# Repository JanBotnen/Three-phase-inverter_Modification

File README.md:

# Three-phase-inverter_Modification

**Design and implementation of a three-phase inverter with SPWM and SVPWM, prepared for future PMSM control.**

## Background
This project focuses on the continued development and modification of a three-phase DC-to-AC converter, utilizing the Space Vector Pulse Width Modulation (SV-PWM) algorithm.
The inverter was originally designed and built by a previous bachelor group at the Western Norway University of Applied Sciences, and later further refined by another group who successfully reduced the physical footprint of the design.

Their thesis can be found at:
Version 1 : [HVL Open](https://hdl.handle.net/11250/3105460)
Version 2 : [HVL Open](https://hdl.handle.net/11250/3147156)

## About the Project

Building upon their work, our bachelor group aimed to prepare the inverter for future implementation of Field Oriented Control (FOC).  
Throughout this project, our primary goal has been to implement current measurement on all three phases and enable encoder input handling for rotor position feedback.

Our thesis can be found at: 
https://hdl.handle.net/11250/3202875

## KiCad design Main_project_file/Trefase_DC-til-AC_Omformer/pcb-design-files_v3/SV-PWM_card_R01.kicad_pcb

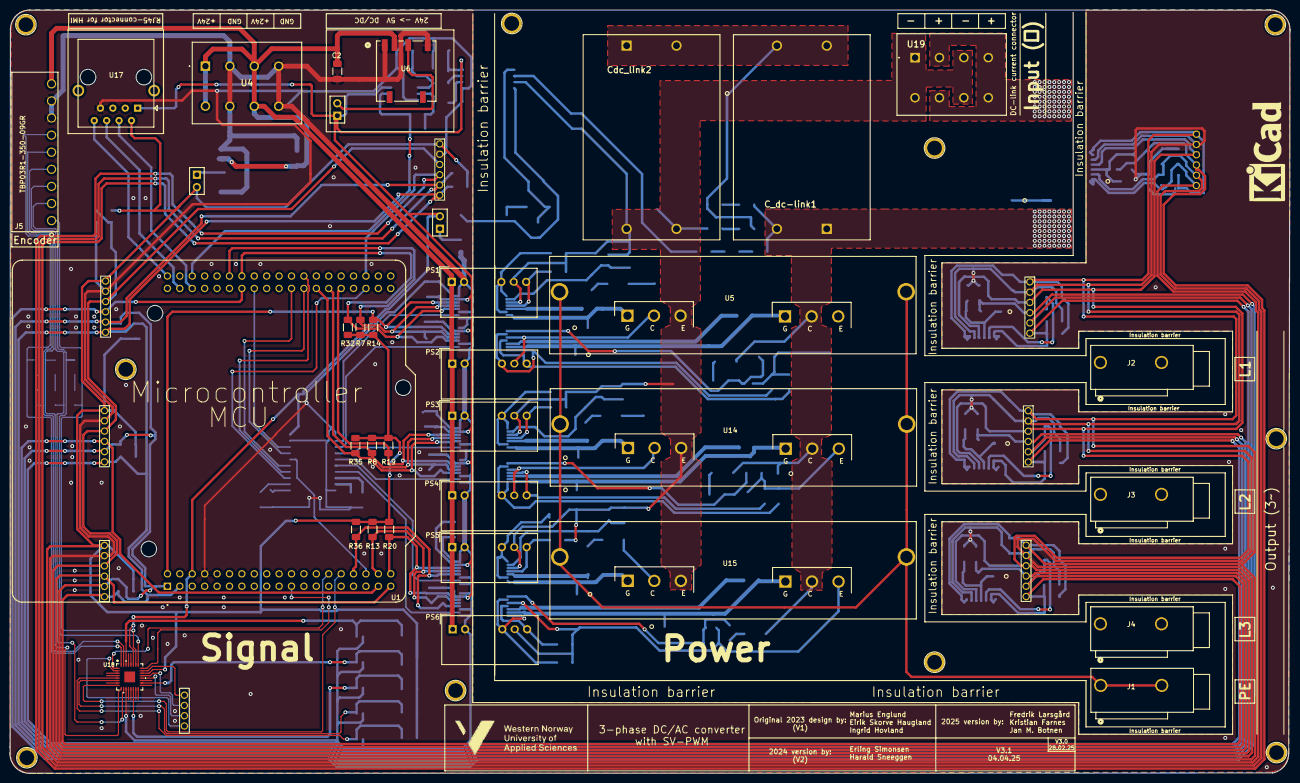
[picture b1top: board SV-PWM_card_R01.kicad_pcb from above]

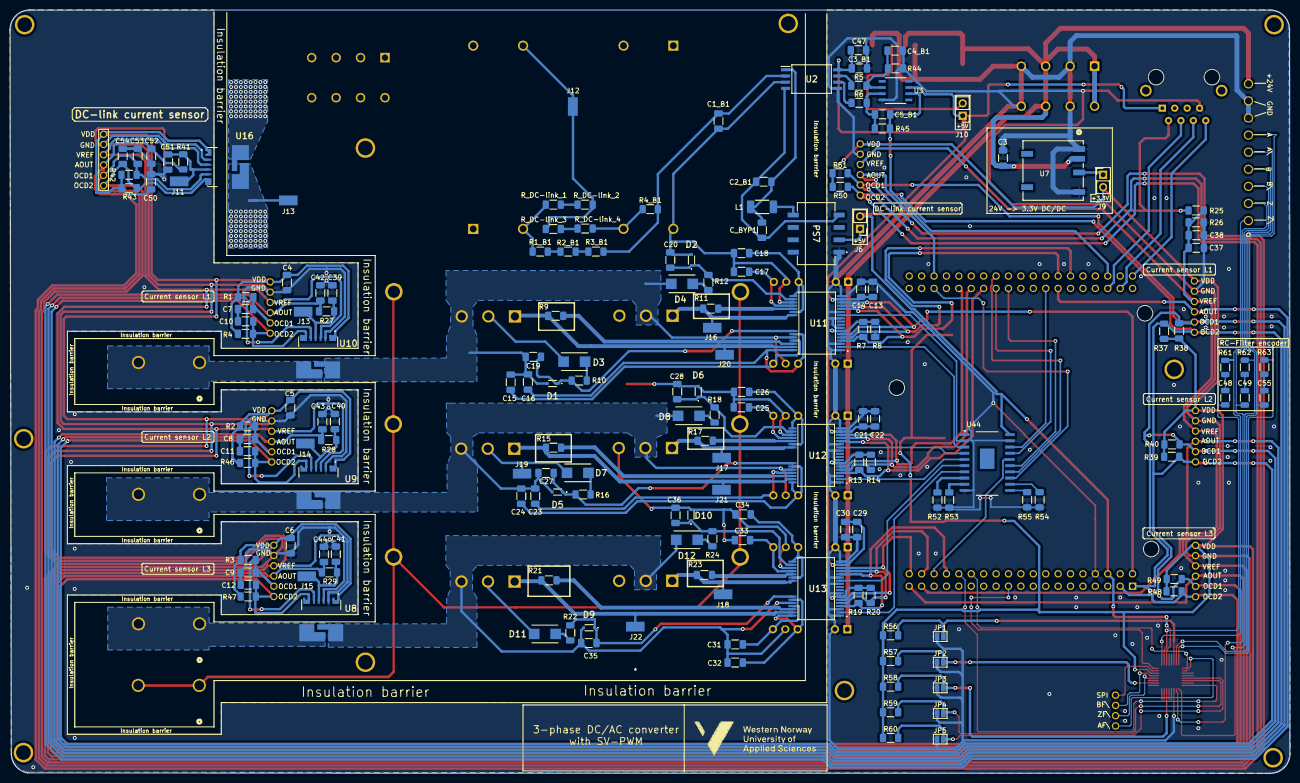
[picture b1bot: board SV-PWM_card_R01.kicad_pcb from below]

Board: 2 copper layers, 262.0 x 156.2 mm, 218 parts (168 on the bottom side), 126 nets.

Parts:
C1_B1: 100p; C_1206_3216Metric_Pad1.33x1.80mm_HandSolder
C2: 10u; C_1206_3216Metric_Pad1.33x1.80mm_HandSolder
C2_B1, C3_B1, C4_B1, C5_B1, C13, C14, C21, C22, C29, C30, C47: 100n; C_1206_3216Metric_Pad1.33x1.80mm_HandSolder
C3: 22u; C_1206_3216Metric_Pad1.33x1.80mm_HandSolder
C4, C5, C6, C50: 220n; C_1206_3216Metric_Pad1.33x1.80mm_HandSolder
C7, C8, C9, C10, C11, C12, C53, C54: 1n; C_1206_3216Metric_Pad1.33x1.80mm_HandSolder
C15, C16, C17, C18, C23, C24, C25, C26, C31, C32, C33, C34: 1u; C_1206_3216Metric_Pad1.33x1.80mm_HandSolder
C19, C20, C27, C28, C35, C36: 220p; C_1206_3216Metric_Pad1.33x1.80mm_HandSolder
C37, C38, C42, C43, C44, C52: 6.8n; C_1206_3216Metric_Pad1.33x1.80mm_HandSolder
C39, C40, C41, C51: 15n; C_1206_3216Metric_Pad1.33x1.80mm_HandSolder
C48, C49, C55: 100p; C_1206_3216Metric
C_BYP1: 4.7u; C_1206_3216Metric_Pad1.33x1.80mm_HandSolder
C_dc-link1: 14u; DC-link-capacitor-B32776G0146K000
Cdc_link2: 14u; DC-link-capacitor-B32776G0146K000
D1, D2, D5, D6, D9, D10: D_Schottky; Schottky-BAT165AX
D3, D4, D7, D8, D11, D12: D; Diode-SMBJ50CA
H6, H6#2, H6#3, H7, H7#2, H7#3, H7#4, H7#5, H7#6, H8: MountingHole; Skru-hull_3mm
J1, J2, J3, J4: WAGO_2606-1101; CONN_2606-1101_WAG
J5: TBP03R1-350-09GR; TBP03R1-350-03GR
J6, J9, J10: Conn_01x02_Male; PinHeader_1x02_P2.54mm_Vertical
J11, J12, J13, J13#2, J14, J15, J16, J17, J18, J19, J20, J21, J22: 5019; Keystone-5019
J23: 2606-1106/010-000; 6PinHeaderConnector_Strømsensor
JP1, JP2, JP3, JP4, JP5: SolderJumper_2_Open; SolderJumper-2_P1.3mm_Open_Pad1.0x1.5mm
L1: 47u; L_2010_5025Metric_Pad1.52x2.65mm_HandSolder
PS1, PS2, PS3, PS4, PS5, PS6: MGJ2D241509SC; Converter_DCDC_Murata_MGJ2DxxxxxxSC_THT
PS7: NTE0505MC; DC-DC-NTE0505MC
R1, R2, R3, R4, R7, R7#2, R8, R8#2, R13, R13#2, R14, R14#2, R19, R19#2, R20, R20#2, R32, R35, R36, R42, R43, R46, R47: 4.7k; R_1206_3216Metric_Pad1.30x1.75mm_HandSolder
R1_B1, R2_B1, R3_B1: 500k; R_1206_3216Metric_Pad1.30x1.75mm_HandSolder
R4_B1: 3.75k; R_1206_3216Metric_Pad1.30x1.75mm_HandSolder
R5, R6, R52, R53, R54, R55: 10k; R_1206_3216Metric_Pad1.30x1.75mm_HandSolder
R9, R11, R15, R17, R21, R23: 10; R_1206_3216Metric_Pad1.30x1.75mm_HandSolder
R10, R12, R16, R18, R22, R24, R25, R26: 1k; R_1206_3216Metric_Pad1.30x1.75mm_HandSolder
R27, R28, R29, R41: 220; R_1206_3216Metric_Pad1.30x1.75mm_HandSolder
R37, R38, R39, R40, R48, R49, R50, R51, R56, R57, R58, R59, R60: R; R_1206_3216Metric_Pad1.30x1.75mm_HandSolder
R44, R45: 16.5k; R_1206_3216Metric_Pad1.30x1.75mm_HandSolder
R61, R62, R63: 270; R_1206_3216Metric
R_DC-link_1, R_DC-link_2, R_DC-link_3, R_DC-link_4: ???; R_1206_3216Metric_Pad1.30x1.75mm_HandSolder
U1: MCU; MODULE_NUCLEO-L476RG
U2: ACPL-C87B-000E; ACPL-SOIC127P1150X331-8N
U3: type="X" model="OPAMP" lib=""; D8
U4, U19: Wago_2604-3104; WAGO-26043104
U5: Inverter leg nr 1; Inverter leg
U6: MP-K7805T-500R3; TRN 1&slash_3SM_SINGLE_TRP
U7: TRN 1-2410SM; TRN 1&slash_3SM_SINGLE_TRP
U8, U9, U10, U16: TLI4971A050T5UE0001XUMA1
U11, U12, U13: Infineon_2ED020I12-F2; GateDriver-2ED020I12F2XUMA1
U14: Inverter leg nr 2; Inverter leg
U15: Inverter leg nr 3; Inverter leg
U17: RJ45_Connector_MCU-til-HMI; RJ45_Amphenol_54602-x08_Horizontal
U18: MAX14890EATJ+T; 21-0140_T3255&plus_6_MXM_Encoder_chip
U36: PinConector_DC-link; 6PinHeaderConnector_Strømsensor
U37: PinConnector_L1-sensor; 6PinHeaderConnector_Strømsensor
U38: PinConnector_L2-sensor; 6PinHeaderConnector_Strømsensor
U39: PinConnector_L3-sensor; 6PinHeaderConnector_Strømsensor
U40: PinConector_MCU-til-L1; 6PinHeaderConnector_Strømsensor
U41: PinConnector_MCU-til-L2; 6PinHeaderConnector_Strømsensor
U42: PinConnector_MCU-til-L3; 6PinHeaderConnector_Strømsensor
U43: PinConnector_MCU-til-DClink; 6PinHeaderConnector_Strømsensor
U44: SN54HCT245_BusTranciver; ETSSOP-20-1EP_4.4x6.5mm_P0.65mm_EP3x4.2mm_ny123

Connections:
+3.3V: C4.1, C5.1, C6.1, C50.2, J9.1, J9.2, R1.1, R2.1, R3.1, R4.1, R7.1, R8.1, R13.1, R14.1, R19.1, R20.1, R25.1, R32.1, R35.1, R36.1, R37.1, R38.1, R39.1, R40.1, R42.1, R43.1, R46.1, R47.1, R48.1, R49.1, R50.1, R51.1, R56.1, R57.1, R58.1, R59.1, R60.1, U7.3 (NC), U8.1 (VDD), U9.1 (VDD), U10.1 (VDD), U16.1 (VDD), U17.2 (5V), U18.22 (VL), U36.1 (VDD), U37.1 (VDD), U38.1 (VDD), U39.1 (VDD), U40.1 (VDD), U41.1 (VDD), U42.1 (VDD), U43.1 (VDD)
+5V: C3_B1.1, C13.1, C14.2, C21.1, C22.2, C29.1, C30.2, C47.1, J6.2, J10.1, R7#2.2, R8#2.2, R13#2.2, R14#2.2, R19#2.2, R20#2.2, U1.CN7_6 (E5V), U2.8 (VDD2), U3.7, U11.7 (VCC1HS), U11.17 (VCC1LS), U12.7 (VCC1HS), U12.17 (VCC1LS), U13.7 (VCC1HS), U13.17 (VCC1LS), U17.1 (3.3V), U18.27 (VCC), U44.20 (VCC)
+5V_ISO: C2_B1.1, C_BYP1.1, L1.2, U2.1 (VDD1)
+15 V (1): C17.1, PS1.7 (+VOUT), U11.22 (VCC2LS)
+15 V (2): C15.2, PS2.7 (+VOUT), U11.33 (VCC2HS)
+15 V (3): C25.1, PS3.7 (+VOUT), U12.22 (VCC2LS)
+15 V (4): C23.2, PS4.7 (+VOUT), U12.33 (VCC2HS)
+15 V (5): C33.1, PS5.7 (+VOUT), U13.22 (VCC2LS)
+15 V (6): C31.2, PS6.7 (+VOUT), U13.33 (VCC2HS)
+24V: C2.1, C3.1, J5.9, PS1.1 (+VIN), PS2.1 (+VIN), PS3.1 (+VIN), PS4.1 (+VIN), PS5.1 (+VIN), PS6.1 (+VIN), U4.1, U4.2, U4.5, U4.6, U6.2 (+Vin), U7.2 (SENSE)
+DC-link: U16.8 (IP+), U19.3, U19.4, U19.7, U19.8
-8.7 V (1): C18.1, PS1.5 (-VOUT), U11.19 (VEE2LS), U11.24 (VEE2LS)
-8.7 V (2): C16.1, PS2.5 (-VOUT), U11.31 (VEE2HS), U11.36 (VEE2HS)
-8.7 V (3): C26.1, PS3.5 (-VOUT), U12.19 (VEE2LS), U12.24 (VEE2LS)
-8.7 V (4): C24.1, PS4.5 (-VOUT), U12.31 (VEE2HS), U12.36 (VEE2HS)
-8.7 V (5): C34.1, PS5.5 (-VOUT), U13.19 (VEE2LS), U13.24 (VEE2LS)
-8.7 V (6): C32.1, PS6.5 (-VOUT), U13.31 (VEE2HS), U13.36 (VEE2HS)
/CurrentMeasurement/L1 (out): J2.1, J2.2 (1), U10.7 (IP-)
/CurrentMeasurement/L2 (out): J3.1, J3.2 (1), U9.7 (IP-)
/CurrentMeasurement/L3 (out): J4.1, J4.2 (1), U8.7 (IP-)
/GateDriver1/OUTHS: J20.1, R9.1, U5.2 (Gate_HS), U11.35 (CLAMPHS)
/GateDriver1/OUTLS: J16.1, R11.1, U5.5 (Gate_LS), U11.25 (CLAMPLS)
/GateDriver2/OUTHS: J21.1, R15.1, U12.35 (CLAMPHS), U14.2 (Gate_HS)
/GateDriver2/OUTLS: J17.1, R17.1, U12.25 (CLAMPLS), U14.5 (Gate_LS)
/GateDriver3/OUTHS: J22.1, R21.1, U13.35 (CLAMPHS), U15.2 (Gate_HS)
/GateDriver3/OUTLS: J18.1, R23.1, U13.25 (CLAMPLS), U15.5 (Gate_LS)
A: J5.6, R63.1, U18.32 (A)
AF\: J23.1, U18.2 (*AFAULT)
AOUT_DC-link: C52.1, R41.2, U1.CN10_34 (PC4), U36.4 (AOUT), U43.4 (AOUT)
AOUT_L1: C42.1, R27.2, U1.CN10_13 (PA6), U37.4 (AOUT), U40.4 (AOUT)
AOUT_L2: C43.1, R28.2, U1.CN7_35 (PC2), U38.4 (AOUT), U41.4 (AOUT)
AOUT_L3: C44.1, R29.2, U1.CN7_37 (PC3), U39.4 (AOUT), U42.4 (AOUT)
A\: C55.2, J5.5, U18.31 (*A)
B: J5.4, R62.1, U18.9 (B)
BF\: J23.3, U18.21 (*BFAULT)
B\: C49.2, J5.3, U18.10 (*B)
COM (1): C1_B1.2, C17.2, C18.2, C20.2, C25.2, C26.2, C28.2, C33.2, C34.2, C36.2, Cdc_link2.2, Cdc_link2.4, D2.2 (A), D6.2 (A), D10.2 (A), PS1.6 (0V), PS3.6 (0V), PS5.6 (0V), R4_B1.1, R_DC-link_4.2, U2.3 (SDHN), U5.6 (Emitter_LS), U11.21 (GND2LS), U12.21 (GND2LS), U13.21 (GND2LS), U14.6 (Emitter_LS), U15.6 (Emitter_LS), U19.1, U19.2, U19.5, U19.6
COM (2): C15.1, C16.2, C19.2, D1.2 (A), D4.1 (K), PS2.6 (0V), U5.3 (Emitter_HS), U5.4 (Collector_LS), U10.8 (IP+), U11.32 (GND2HS)
COM (4): C23.1, C24.2, C27.2, D5.2 (A), D8.1 (K), PS4.6 (0V), U9.8 (IP+), U12.32 (GND2HS), U14.3 (Emitter_HS), U14.4 (Collector_LS)
COM (6): C31.1, C32.2, C35.2, D9.2 (A), D12.1 (K), PS6.6 (0V), U8.8 (IP+), U13.32 (GND2HS), U15.3 (Emitter_HS), U15.4 (Collector_LS)
C_DC-link: C_dc-link1.2, C_dc-link1.4, Cdc_link2.1, Cdc_link2.3, J12.1, R_DC-link_2.2, R_DC-link_3.1
DC-LINK-VOLTAGE: C1_B1.1, R3_B1.1, R4_B1.2, U2.2 (VIN)
Earth_Protective: J1.1, J1.2 (1), U5.7 (Heatsink_THT1), U5.8 (Heatsink_THT2), U14.7 (Heatsink_THT1), U14.8 (Heatsink_THT2), U15.7 (Heatsink_THT1), U15.8 (Heatsink_THT2)
GND: C2.2, C3.2, C3_B1.2, C4.2, C4_B1.2, C5.2, C6.2, C7.1, C8.1, C9.1, C10.1, C11.1, C12.1, C13.2, C14.1, C21.2, C22.1, C29.2, C30.1, C37.2, C38.2, C39.2, C40.2, C41.2, C42.2, C43.2, C44.2, C47.2, C50.1, C51.2, C52.2, C53.1, C54.1, J5.7, J5.8, JP1.1 (A), JP2.1 (A), JP3.1 (A), JP4.1 (A), JP5.1 (A), PS1.2 (-VIN), PS2.2 (-VIN), PS3.2 (-VIN), PS4.2 (-VIN), PS5.2 (-VIN), PS6.2 (-VIN), PS7.1 (-VIN), R26.2, R44.2, R52.2, R53.2, R54.2, R55.2, U1.CN7_8 (GND), U2.5 (GND2), U3.4 (-), U4.3, U4.4, U4.7, U4.8, U6.1 (+Vin), U6.5 (+Vout), U7.1 (Q), U7.5 (EN), U8.2 (GND), U9.2 (GND), U10.2 (GND), U11.1 (GND1), U11.3 (INHS-), U11.8 (GND1), U11.11 (GND1), U11.13 (INLS-), U11.18 (GND1), U12.1 (GND1), U12.3 (INHS-), U12.8 (GND1), U12.11 (GND1), U12.13 (INLS-), U12.18 (GND1), U13.1 (GND1), U13.3 (INHS-), U13.8 (GND1), U13.11 (GND1), U13.13 (INLS-), U13.18 (GND1), U16.2 (GND), U17.7 (GND), U18.11 (GND), U36.2 (GND), U37.2 (GND), U38.2 (GND), U39.2 (GND), U40.2 (GND), U41.2 (GND), U42.2 (GND), U43.2 (GND), U44.1 (DIR), U44.10 (GND), U44.19 (/OE)
GND_ISO: C2_B1.2, C_BYP1.2, PS7.7 (-VOUT), U2.4 (GND1)
INT_HMI-card: U1.CN10_2 (PC8), U17.8 (INT)
I/O_DI_FLT-1: R7.2, R8#2.1, U1.CN10_12 (PA12), U11.5 (/FLTHS), U11.15 (/FLTLS)
I/O_DI_FLT-2: R8.2, R14#2.1, U1.CN10_27 (PB4), U12.5 (/FLTHS), U12.15 (/FLTLS)
I/O_DI_FLT-3: R13.2, R20#2.1, U1.CN7_36 (PC1), U13.5 (/FLTHS), U13.15 (/FLTLS)
I/O_DI_RDY-1: R7#2.1, R32.2, U1.CN10_14 (PA11), U11.4 (RDYHS), U11.14 (RDYLS)
I/O_DI_RDY-2: R13#2.1, R35.2, U1.CN10_25 (PB10), U12.4 (RDYHS), U12.14 (RDYLS)
I/O_DI_RDY-3: R19#2.1, R36.2, U1.CN7_32 (PA4), U13.4 (RDYHS), U13.14 (RDYLS)
I/O_DO_INHS-1: U11.2 (INHS+), U44.3 (A2)
I/O_DO_INHS-2: U12.2 (INHS+), U44.5 (A4)
I/O_DO_INHS-3: U13.2 (INHS+), U44.7 (A6)
I/O_DO_INLS-1: U11.12 (INLS+), U44.2 (A1)
I/O_DO_INLS-2: U12.12 (INLS+), U44.4 (A3)
I/O_DO_INLS-3: U13.12 (INLS+), U44.6 (A5)
I/O_DO_RS-1: R14.2, U1.CN7_2 (PC11), U11.6 (/RSTHS), U11.16 (/RSTLS)
I/O_DO_RS-2: R19.2, U1.CN10_29 (PB5), U12.6 (/RSTHS), U12.16 (/RSTLS)
I/O_DO_RS-3: R20.2, U1.CN7_38 (PC0), U13.6 (/RSTHS), U13.16 (/RSTLS)
unnamed: C48.1, R61.2
unnamed: C49.1, R62.2
unnamed: C55.1, R63.2
unnamed: C19.1, D1.1 (K), R10.2, U11.30 (DESATHS)
unnamed: C20.1, D2.1 (K), R12.2, U11.20 (DESATLS)
unnamed: D3.2 (A), R10.1
unnamed: D4.2 (A), R12.1
unnamed: C27.1, D5.1 (K), R16.2, U12.30 (DESATHS)
unnamed: C28.1, D6.1 (K), R18.2, U12.20 (DESATLS)
unnamed: D7.2 (A), R16.1
unnamed: D8.2 (A), R18.1
unnamed: C35.1, D9.1 (K), R22.2, U13.30 (DESATHS)
unnamed: C36.1, D10.1 (K), R24.2, U13.20 (DESATLS)
unnamed: D11.2 (A), R22.1
unnamed: D12.2 (A), R24.1
unnamed: J6.1, PS7.3 (+VIN_)
unnamed: J10.2, U6.3 (GND)
unnamed: JP1.2 (B), R56.2, U18.30 (DI/TTL3)
unnamed: JP2.2 (B), R57.2, U18.18 (DI/TTLY)
unnamed: JP3.2 (B), R58.2, U18.14 (DI/TTL2)
unnamed: JP4.2 (B), R59.2, U18.6 (TTL/SDI)
unnamed: JP5.2 (B), R60.2, U18.5 (SNGL/CLK)
unnamed: L1.1, PS7.8 (+VOUT)
unnamed: R1_B1.2, R2_B1.1
unnamed: R2_B1.2, R3_B1.2
unnamed: R_DC-link_1.2, R_DC-link_2.1
unnamed: R_DC-link_3.2, R_DC-link_4.1
unnamed: R5.1, U2.7 (VOUT+)
unnamed: R6.1, U2.6 (VOUT-)
unnamed: C4_B1.1, R5.2, R44.1, U3.2 (V-)
unnamed: C5_B1.2, R6.2, R45.2, U3.3 (+)
unnamed: C41.1, J15.1, R29.1, U8.4 (AOUT)
unnamed: C40.1, J14.1, R28.1, U9.4 (AOUT)
unnamed: C39.1, J13#2.1, R27.1, U10.4 (AOUT)
unnamed: R9.2, U11.34 (OUTHS)
unnamed: R11.2, U11.23 (OUTLS)
unnamed: R15.2, U12.34 (OUTHS)
unnamed: R17.2, U12.23 (OUTLS)
unnamed: R21.2, U13.34 (OUTHS)
unnamed: R23.2, U13.23 (OUTLS)
unnamed: C51.1, J11.1, R41.1, U16.4 (AOUT)
unnamed: R52.1, U44.8 (A7)
unnamed: R53.1, U44.9 (A8)
unnamed: R54.1, U44.12 (B7)
unnamed: R55.1, U44.11 (B8)
OCD1: C7.2, C8.2, C9.2, C53.2, R1.2, R2.2, R3.2, R38.2, R40.2, R42.2, R49.2, R51.2, U1.CN7_1 (PC10), U8.5 (ICD1), U9.5 (ICD1), U10.5 (ICD1), U16.5 (ICD1), U36.5 (OCD1), U37.5 (OCD1), U38.5 (OCD1), U39.5 (OCD1), U40.5 (OCD1), U41.5 (OCD1), U42.5 (OCD1), U43.5 (OCD1)
OCD2: C10.2, C11.2, C12.2, C54.2, R4.2, R37.2, R39.2, R43.2, R46.2, R47.2, R48.2, R50.2, U1.CN7_3 (PC12), U8.6 (OCD2), U9.6 (OCD2), U10.6 (OCD2), U16.6 (OCD2), U36.6 (OCD2), U37.6 (OCD2), U38.6 (OCD2), U39.6 (OCD2), U40.6 (OCD2), U41.6 (OCD2), U42.6 (OCD2), U43.6 (OCD2)
PA0: U1.CN7_28 (PA0), U18.1 (AO)
PA1: U1.CN7_30 (PA1), U18.8 (BO)
PA7: U1.CN10_15 (PA7), U44.18 (B1)
PA8: U1.CN10_23 (PA8), U44.17 (B2)
PA9: U1.CN10_21 (PA9), U44.15 (B4)
PA10: U1.CN10_33 (PA10), U44.13 (B6)
PB0: U1.CN7_34 (PB0), U44.16 (B3)
PB1: U1.CN10_24 (PB1), U44.14 (B5)
PB7: U1.CN7_21 (PB7), U18.24 (ZO)
PB8: U1.CN10_3 (PB8), U17.6 (SCL)
PB9: U1.CN10_5 (PB9), U17.4 (SDA)
PC5: C5_B1.1, R45.1, U1.CN10_6 (PC5), U3.6
SPI: J23.4, U18.23 (SPI)
TA+1_HS: C_dc-link1.1, C_dc-link1.3, D3.1 (K), D7.1 (K), D11.1 (K), J13.1, J19.1, R1_B1.1, R_DC-link_1.1, U5.1 (Collector_HS), U14.1 (Collector_HS), U15.1 (Collector_HS), U16.7 (IP-)
VREF: C37.1, C38.1, R25.2, R26.1, U8.3 (VREF), U9.3 (VREF), U10.3 (VREF), U16.3 (VREF), U36.3 (VREF), U37.3 (VREF), U38.3 (VREF), U39.3 (VREF), U40.3 (VREF), U41.3 (VREF), U42.3 (VREF), U43.3 (VREF)
Z: J5.2, R61.1, U18.25 (Z)
ZF\: J23.2, U18.20 (*ZFAULT)
Z\: C48.2, J5.1, U18.26 (*Z)

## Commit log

2025-05-17 Create source-code
2025-05-17 Create Placeholder
2025-05-17 Create initial commit
2025-05-21 Lagt til KiCad prosjekt

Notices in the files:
parts and their libraries:
Copyright 2016 Accelerated Designs. All rights reserved.
Copyright 2021 Accelerated Designs. All rights reserved.
